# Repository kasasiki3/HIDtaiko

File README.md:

# HIDtaiko 
#### 低価格で高性能なおうち太鼓プロジェクト
#### HIDtaikoでは[基盤](drumhead/readme_drumhead.md)、[接続器](HIDtaiko_connector_rp2040/rp2040readme.md)の設計を行っています。

[English README](README_EN.md)

# ◇readme構造
<pre>
.
└── README.md(メイン)
    ├── rp2040readme.md(RP2040接続器の組み立て方、詳細)
    ├── readme_drumhead.md(基盤、詳細)

</pre>

# ◇接続器

> ## [→ RP2040接続器 組み立てガイド](HIDtaiko_connector_rp2040/rp2040readme.md)
> **最新・最安・最高性能のおすすめモデル**（最安800円〜、簡単なはんだ付けのみ）

## 各接続器の比較表
| 項目| 1.2接続器|1.3接続器|2.0接続器| [RP2040接続器](HIDtaiko_connector_rp2040/rp2040readme.md)|
|-----|---------|-------|-----------------|-----|
| 対応デバイス     | PC, Switch | PC| PC, Switch| PC,(switchに対応予定) |
| 感度変更方法     |感度変更サイトで変更可能| 感度変更サイトで変更可能 | 接続器単体で変更可能 | 感度変更サイトで変更可能 |
| ファームウェア   | Arduino IDE| Arduino IDE|Arduino IDE| Pico SDK|
| 回路             | 簡易的な1MΩ抵抗| 簡易的な1MΩ抵抗| オペアンプによる信号の増幅| ショットキーバリアダイオードクランプ回路|
| 改造のしやすさ   | 簡単| 簡単| 簡単| 難しい|
| 制作難易度       | 中〜高（Arduinoの知識が必要）| 中〜高（Arduinoの知識が必要）| 中〜高（Arduinoの知識が必要）| 低（簡単なはんだ付けのみでOK|
| 制作費用         | 最低構成1500円程度| 最低構成1500円程度| 最低構成2200円程度|最安800円程度|
| 補足             | Switchで使いたい人におすすめ|-|※原因不明の無反応が発生することあり| ※最も新しく、性能も最も高いおすすめモデル   |
| プレイ動画       |[動画を見る](https://www.youtube.com/watch?v=cY1Ix29XORo)| [動画を見る](https://www.youtube.com/watch?v=Z8ZBOPpMMD8) | [動画を見る](https://www.youtube.com/watch?v=VVSo0jgkqcQ)| [動画を見る](https://www.youtube.com/watch?v=wMSDLN9h2Co)|

# ◇感度変更サイト

**[→ 感度変更サイトを開く](https://kasasiki3.github.io/HIDtaiko/v12.html)**（Chrome / Edge のみ対応）

接続器を PC に繋いだままブラウザから感度・ディレイを調整できます。V1.1（RP2040）・V1.2 に対応。

## 仕組み

```
ピエゾ → ADC（アナログ読み取り）→ 差分検出 → 閾値判定 → キー入力
```

ピエゾが振動すると電圧が変化します。マイコンは直前サンプルとの差分（デルタ）を計算し、設定した閾値（感度）を超えたときにキー入力を発生させます。

誤検出を防ぐためのタイマー（Delay）も持っており、入力後の一定時間は同センサーや隣接センサーからの入力を無視します。

| パラメータ | 役割 |
|---|---|
| 感度（Sensitivity） | デルタがこの値を超えると入力。値が大きいほど感度が低い |
| Adelay | 同センサーの再入力クールダウン |
| Bdelay | 面（ドン）共有クールダウン |
| Cdelay | 縁（カッ）共有クールダウン |
| Ddelay | 面打後に縁を、縁打後に面を無視する時間 |

# ◇[基盤の作り方](drumhead/readme_drumhead.md)

## webサイトで基盤のデザインを確認できます:[基盤3Dデータ](https://a360.co/4iZLSSL)

## 基盤の制作方法→記事:[zeen](https://zenn.dev/kasashiki/articles/7bf286b8120f90) 動画:[youtube](https://www.youtube.com/watch?v=5O0MgKzX0PY)

## 特徴
| 項目 | 内容 |
|------|------|
| AC基盤との互換性 | 無 |
| 鉄板・スポンジ・樽| 使用できません |
| 対応面 | AC面・太鼓フォース面|
| 制作所要時間 | 約2〜3時間 |

# ◇センサ
## センサの比較

GSS-4SAとAT3040どちらもしっかりと固定することで弱い力でも反応します。しかし、GSS-4SAの方が性能が良いです。設定に余裕が生まれます。価格にかなり差があるため、最初はAT3040センサを購入することをお勧めします。

### [センサ組み立てガイド](drumhead/sensor.md)

# 質問はXのDMにお願いします。
[lit.link](https://lit.link/kasashiki)

## License
*** by kasashiki is licensed under the Apache License, Version2.0

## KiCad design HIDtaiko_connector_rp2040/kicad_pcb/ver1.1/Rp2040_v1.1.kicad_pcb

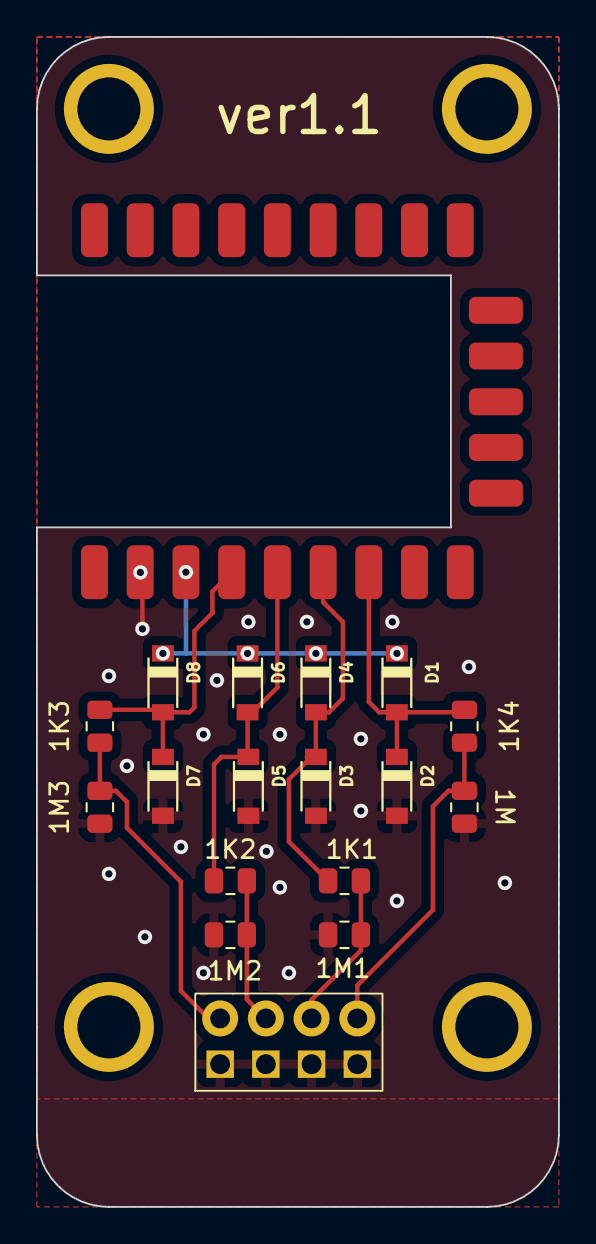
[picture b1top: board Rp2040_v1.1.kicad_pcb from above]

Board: 2 copper layers, 29.0 x 65.0 mm, 22 parts (0 on the bottom side), 10 nets.

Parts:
1K1, 1K2, 1K3, 1K4, 1M1, 1M2, 1M3, 1M4: R; R_0805_2012Metric
D1, D2, D3, D4, D5, D6, D7, D8: MBR0520LT1G; SOD3716X135N
J2, J2#2, J2#3, J2#4: M3; m3 nezi
U1: rp2040_micro_board
U2: PinHeader_2x4_P2.54mm

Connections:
+3V3: D1.C, D4.C, D6.C, D8.C, U1.30 (3V)
GND: 1M1.2, 1M2.2, 1M3.2, 1M4.2, D2.A, D3.A, D5.A, D7.A, U1.31 (GND), U2.1, U2.2, U2.3, U2.4
unnamed: 1K4.1, D1.A, D2.C, U1.26 (ADC0)
unnamed: 1K1.1, D3.C, D4.A, U1.27 (ADC1)
unnamed: 1K2.1, D5.C, D6.A, U1.28 (ADC2)
unnamed: 1K3.1, D7.C, D8.A, U1.29 (ADC3)
unnamed: 1K3.2, 1M3.1, U2.5 (1_b)
unnamed: 1K2.2, 1M2.1, U2.6 (2_b)
unnamed: 1K1.2, 1M1.1, U2.7 (3_b)
unnamed: 1K4.2, 1M4.1, U2.8 (4_b)

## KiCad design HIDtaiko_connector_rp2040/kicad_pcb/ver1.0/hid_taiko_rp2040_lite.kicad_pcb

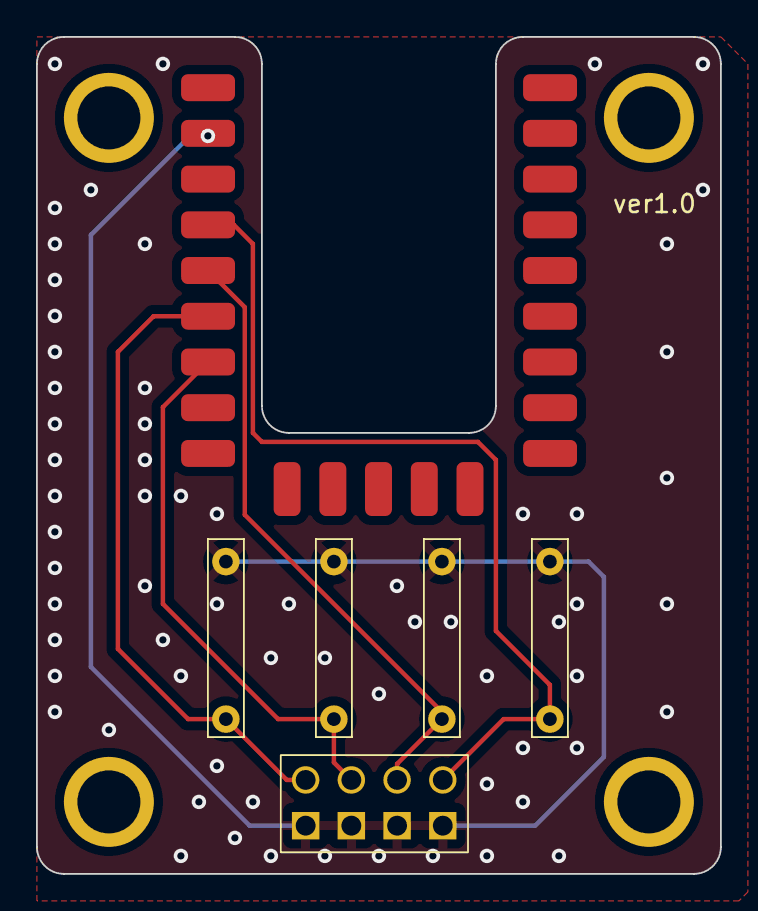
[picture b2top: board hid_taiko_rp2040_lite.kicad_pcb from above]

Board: 2 copper layers, 38.0 x 46.5 mm, 10 parts (0 on the bottom side), 5 nets.

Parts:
J2, J2#2, J2#3, J2#4: Conn_02x05; m3 nezi
U2: PinHeader_2x4_P2.54mm_Vertical_Staggered
U3: rp2040_micro_board
U5, U6, U7, U8: スルーホールの一般的な 抵抗

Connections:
unnamed: U2.5 (1_b), U3.27 (ADC1), U8.1
unnamed: U2.6 (2_b), U3.26 (ADC0), U7.1
unnamed: U2.7 (3_b), U3.28 (ADC2), U6.1
unnamed: U2.8 (4_b), U3.29 (ADC3), U5.1
unnamed: U2.1, U2.2, U2.3, U2.4, U3.31 (GND), U5.2, U6.2, U7.2, U8.2

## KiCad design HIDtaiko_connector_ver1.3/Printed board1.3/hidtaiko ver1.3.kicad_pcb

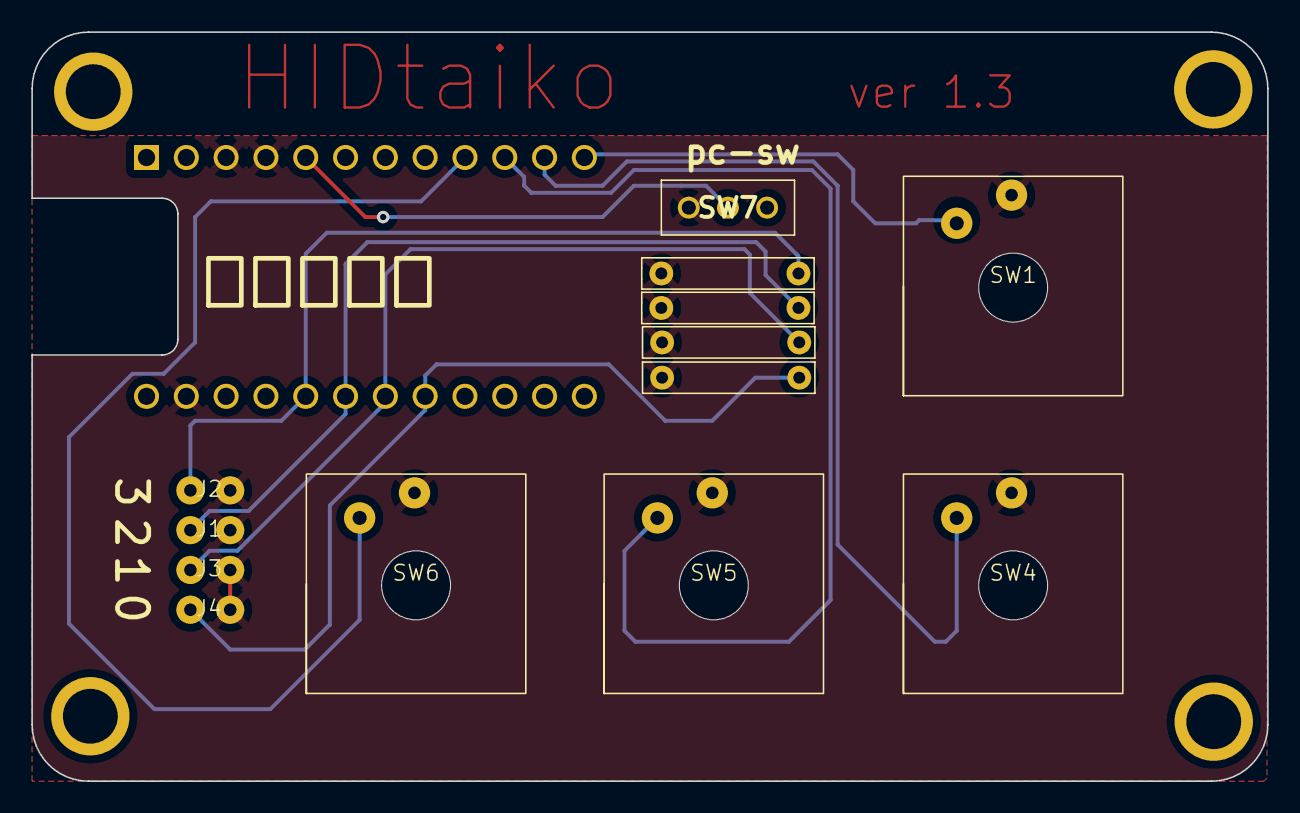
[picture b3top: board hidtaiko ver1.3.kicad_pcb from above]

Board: 2 copper layers, 78.9 x 47.8 mm, 17 parts (1 on the bottom side), 10 nets.

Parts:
J1, J2#3, J3, J4: Conn_01x02_Pin; 2pinHedar
J2, J2#2, J2#4: Conn_02x05; m3 nezi
R1, R2, R3, R4: R; スルーホールの一般的な 抵抗
SW1, SW4, SW5, SW6: SW_PUSH; Redragon smd rgb mx
SW7: swpc; SS12D00G3
U1: ProMicro; ProMicro-NoSilk

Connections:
unnamed: J1.1, R1.1, U1.19 (A2/F5)
unnamed: J1.2, J2#3.2, J3.2, J4.2, R1.2, R2.2, R3.2, R4.2, SW1.2, SW4.2, SW5.2, SW6.2, SW7.1, U1.3 (GND), U1.4 (GND), U1.23 (GND)
unnamed: J2#3.1, R2.1, U1.20 (A3/F4)
unnamed: J3.1, R3.1, U1.18 (A1/F6)
unnamed: J4.1, R4.1, U1.17 (A0/F7)
unnamed: SW4.1, U1.11 (B4/8)
unnamed: SW1.1, U1.12 (B5/9)
unnamed: SW6.1, U1.9 (D7/6)
unnamed: SW5.1, U1.10 (E6/7)
unnamed: SW7.2, U1.5 (SDA/D1/2)

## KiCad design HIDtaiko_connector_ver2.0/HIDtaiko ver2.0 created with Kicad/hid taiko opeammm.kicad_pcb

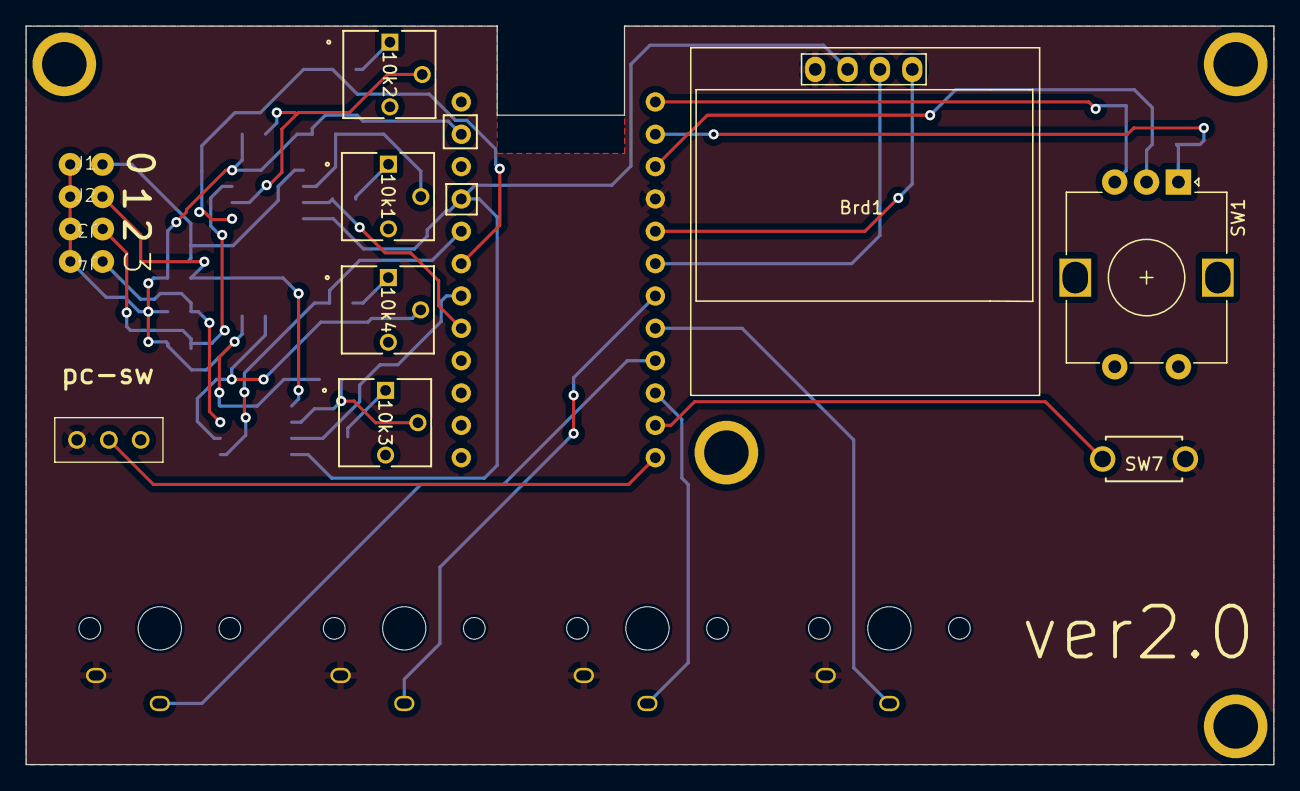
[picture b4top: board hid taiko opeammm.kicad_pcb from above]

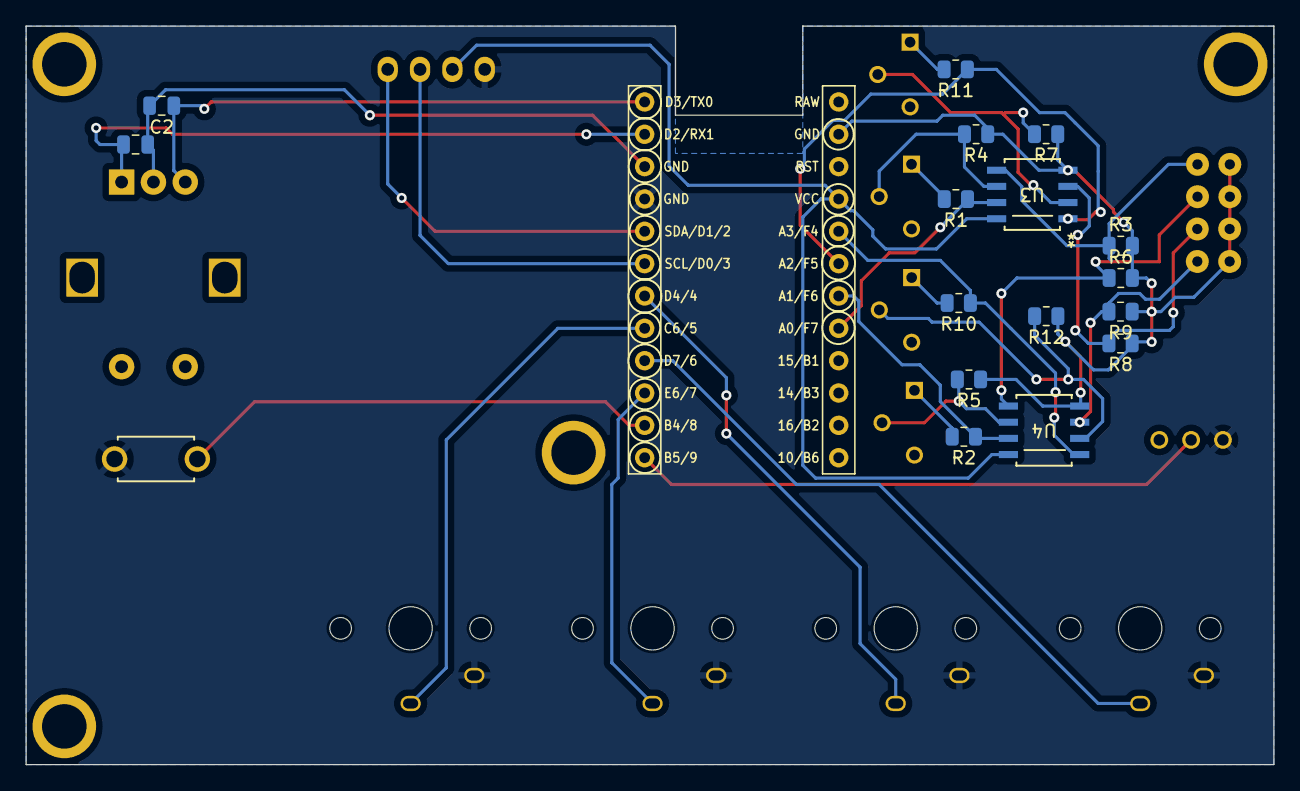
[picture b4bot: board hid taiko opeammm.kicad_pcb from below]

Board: 2 copper layers, 98.0 x 58.0 mm, 34 parts (17 on the bottom side), 30 nets.

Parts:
10k1, 10k2, 10k3, 10k4: Varistor; 3362P
Brd1: SSD1306; 128x64OLED2
C1, C2: C; C_0805_2012Metric
J1, J2, J3, J4: Conn_01x02_Pin; 2pin
J2#2: Conn_02x05; m3 nezi
R1, R2, R4, R5, R7, R10, R11, R12: 10k; R_0805_2012Metric
R3, R6, R8, R9: R; R_0805_2012Metric
SW1: RotaryEncoder; RotaryEncoder_Alps_EC12E-Switch_Vertical_H20mm
SW2: SW_SPDT_321; SS12D00G3
SW3, SW4, SW5, SW6: SW_Push; Kailh_Choc_V1
SW7: SW_Push; SW_PUSH_6x3mm
U1: ProMicro
U3, U4: NJM4580E-ND; NJR-SOP8_NJR

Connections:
unnamed: 10k1.1, R1.2
unnamed: 10k2.1, R11.2
unnamed: 10k3.1, R2.2
unnamed: 10k4.1, R10.2
unnamed: Brd1.1 (GND), SW2.3 (A), SW3.1, SW4.1, SW5.1, SW6.1, SW7.1, U1.4 (GND)
unnamed: Brd1.3 (SCL), U1.6 (SCL/D0/3)
unnamed: Brd1.4 (SDA), U1.5 (SDA/D1/2)
unnamed: Brd1.2 (VCC), U1.21 (VCC), U3.8 (V+), U4.8 (V+)
unnamed: C1.1, C2.2, SW1.C, U1.3 (GND)
unnamed: J1.1, J2.1, J3.2, J4.2, R3.2, R4.1, R5.1, R6.2, R7.1, R8.1, R9.1, R12.1, U1.23 (GND), U3.4 (V-), U4.4 (V-)
unnamed: J1.2, R3.1, U3.5 (BINPUT+)
unnamed: J2.2, R6.1, U4.5 (BINPUT+)
unnamed: J3.1, R8.2, U3.3 (AINPUT+)
unnamed: J4.1, R9.2, U4.3 (AINPUT+)
unnamed: SW2.2 (B), U1.12 (B5/9)
unnamed: R1.1, U1.17 (A0/F7), U3.7 (BOUTPUT)
unnamed: R2.1, U1.18 (A1/F6), U4.7 (BOUTPUT)
unnamed: R11.1, U1.19 (A2/F5), U3.1 (AOUTPUT)
unnamed: R10.1, U1.20 (A3/F4), U4.1 (AOUTPUT)
unnamed: SW7.2, U1.11 (B4/8)
unnamed: SW4.2, U1.8 (C6/5)
unnamed: C1.2, SW1.A, U1.2 (D2/RX1)
unnamed: C2.1, SW1.B, U1.1 (D3/TX0)
unnamed: SW5.2, U1.7 (D4/4)
unnamed: SW3.2, U1.9 (D7/6)
unnamed: SW6.2, U1.10 (E6/7)
unnamed: 10k2.2, R7.2, U3.2 (AINPUT-)
unnamed: 10k1.2, R4.2, U3.6 (BINPUT-)
unnamed: 10k4.2, R12.2, U4.2 (AINPUT-)
unnamed: 10k3.2, R5.2, U4.6 (BINPUT-)

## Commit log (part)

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2023-08-23 Initial commit on master branch
2023-09-24 最初のコミット
2023-10-15 Update sketch_hidtaiko.ino
    感度調節やdelayの調節をしやすくし、ドキムネの連打が1100くらい入ります
2023-10-27 Create LICENSE
2023-10-29 Add files via upload
    swにも対応したhidtaiko接続器のコードです。開発中のため不具合があります。
2023-10-30 Update LICENSE
2023-11-05 テストです。
2023-12-23 dddd
2023-12-23 BOM2
2023-12-24 ver.1.2setuzokuki
2024-02-14 connector case sketch
2024-05-26 ver2.0
2024-05-28 fdfd
2024-06-02 2.0接続器
2024-06-02 2.0接続器完成
2024-06-11 2.0c completed
2024-06-12 1300 ver1.2 for pc
2024-06-13 1.2 1300
2024-06-23 1.2c RM
2024-06-30 1.2 1300 with switch
2024-09-02 official
2024-09-02 add official taiko mode
2024-12-12 ino and kicad file changes
2025-02-12 rp2040接続器の追加
2025-02-14 READMEの更新
2025-02-14 修正README.md
2025-02-15 READMEの編集
2025-02-15 修正 README.md
2025-02-15 original_uf2の追加
2025-02-17 シリアル通信の感度の数値の上限アップ
2025-03-22 arduino接続器のweb感度変更機能を追加(テスト)
2025-04-16 rp2040 多重防止機能追加
2025-04-19 面を叩いた時縁の入力を受け付けない時間の追加
2025-05-05 h delayの修正
2025-05-17 RP2040ver1.1の追加、readmeの追加、センサ説明の追加
2025-05-19 センサ制作手順の追加
2025-05-19 readme 修正
2025-06-02 rp2040zero 接続器制作方法readmeno
2025-12-27 rp2040用2pキーファームウェアの追加
